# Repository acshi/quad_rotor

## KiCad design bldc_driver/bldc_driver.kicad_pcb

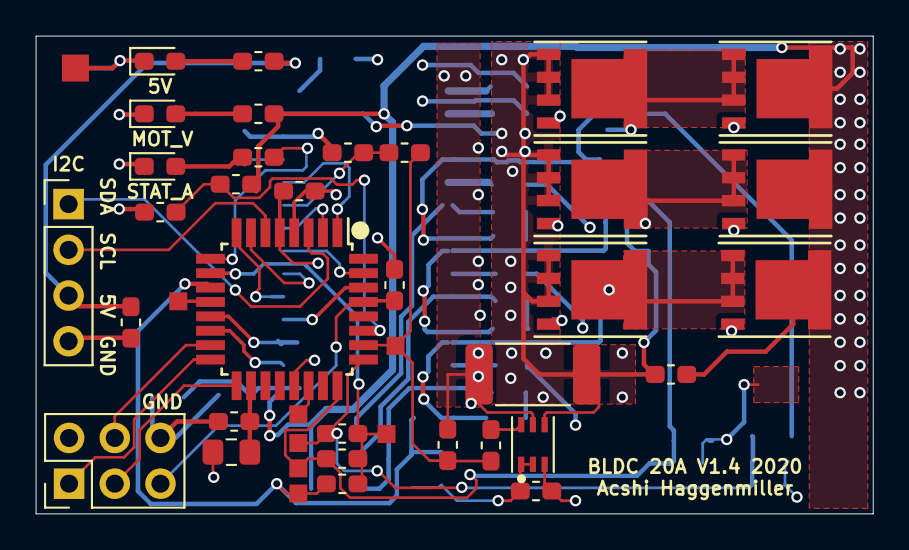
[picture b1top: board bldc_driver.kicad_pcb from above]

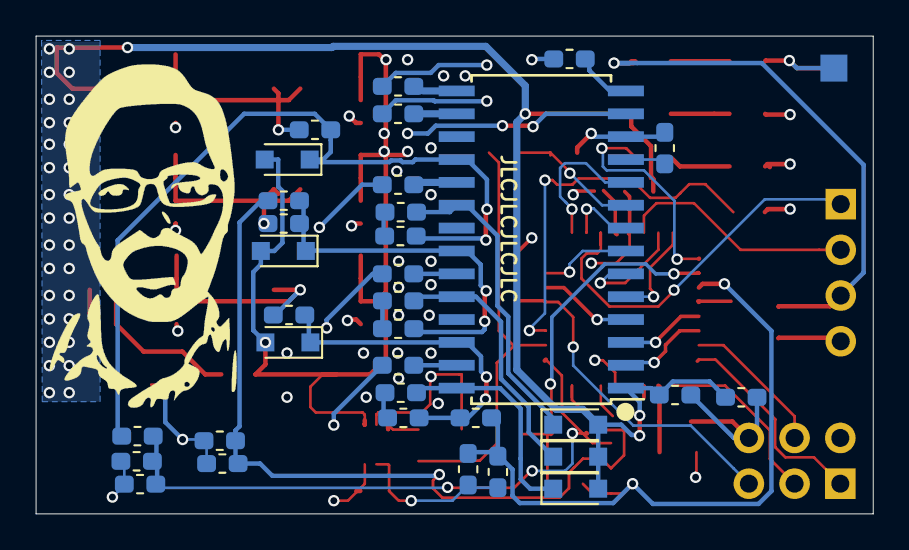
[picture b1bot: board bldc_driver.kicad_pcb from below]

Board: 4 copper layers, 46.5 x 26.5 mm, 67 parts (34 on the bottom side), 56 nets.

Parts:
C2, C5, C6, C16: 100nF; C_0603_1608Metric_Pad1.05x0.95mm_HandSolder
C3, C4, C7, C8: 1uF; C_0603_1608Metric_Pad1.05x0.95mm_HandSolder
C9, C11, C13: 1uF 50V; C_0603_1608Metric_Pad1.05x0.95mm_HandSolder
C10, C12, C14: 22nF; C_0603_1608Metric_Pad1.05x0.95mm_HandSolder
C15: 1nF; C_0603_1608Metric_Pad1.05x0.95mm_HandSolder
D1: Green; LED_0603_1608Metric_Pad1.05x0.95mm_HandSolder
D2: Yellow; LED_0603_1608Metric_Pad1.05x0.95mm_HandSolder
D3: Red; LED_0603_1608Metric_Pad1.05x0.95mm_HandSolder
D4, D5, D6, D7, D8, D9: DSS16UTR‎; D_SOD-323_HandSoldering
J1: I2C 1; PinHeader_1x04_P2.54mm_Vertical
J2: AVR-ISP-6; PinHeader_2x03_P2.54mm_Vertical
L1: 10uH; L_0805_2012Metric_Pad1.15x1.40mm_HandSolder
Q1, Q2, Q3, Q4, Q5, Q6: PSMN0R925YLC; LFPAK_POWER_SO-8
R1, R7: 1k; R_0603_1608Metric_Pad1.05x0.95mm_HandSolder
R2, R6, R11, R18, R22: 4.02k; R_0603_1608Metric_Pad1.05x0.95mm_HandSolder
R3: 3k; R_0603_1608Metric_Pad1.05x0.95mm_HandSolder
R4: 10k; R_0603_1608Metric_Pad1.05x0.95mm_HandSolder
R5, R10, R17, R21: 20k; R_0603_1608Metric_Pad1.05x0.95mm_HandSolder
R8, R12, R19, R23, R24, R25: 1R; R_0603_1608Metric_Pad1.05x0.95mm_HandSolder
R9, R16, R20: 10R; R_0603_1608Metric_Pad1.05x0.95mm_HandSolder
R13, R14, R15: 100k; R_0603_1608Metric_Pad1.05x0.95mm_HandSolder
R26: 20K; R_0603_1608Metric_Pad1.05x0.95mm_HandSolder
R27: 3K; R_0603_1608Metric_Pad1.05x0.95mm_HandSolder
R28, R29, R30: 10; R_0603_1608Metric_Pad1.05x0.95mm_HandSolder
R31: 4mR; R_2512_6332Metric_Pad1.52x3.35mm_HandSolder
U1: ATmega328PB-AU; TQFP-32_7x7mm_P0.8mm
U2: INA199B1; INA199A2
U3: MIC4609; SOIC-28W_7.5x17.9mm_P1.27mm

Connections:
/+5V: C3.1, C4.1, C5.2, J1.3, J2.2, L1.1, R1.2, R4.2, U1.4, U2.3
/+V_MOTOR: C7.2, C8.2, C16.1, D4.2, D5.2, D6.2, Q1.1, Q2.1, Q3.1, R2.2, R5.1, U3.1
/CURRENT: C6.2, R7.1, R26.2, U1.26
/ENABLE: U1.1, U3.10
/HA: U1.14, U3.2
/HB: U1.13, U3.3
/HC: U1.30, U3.4
/LA: U1.8, U3.5
/LB: U1.7, U3.6
/LC: U1.31, U3.7
/MISO: J2.1, U1.16
/MOSI: J2.4, U1.15
/MOTOR_A: C10.1, R10.1, R11.2, R13.2, U1.11
/MOTOR_B: C12.1, R14.2, R17.1, R18.2, U1.24
/MOTOR_C: C14.1, R15.2, R21.1, R22.2, U1.25
/SCK: J2.3, U1.17
/SCL: J1.2, U1.6
/SDA: J1.1, U1.3
/STATUS: R3.2, U1.9
/V_MOT: R5.2, R6.1, U1.27
/bldc_unit1/GHA: Q2.2, R9.1
/bldc_unit1/GHB: Q3.2, R16.1
/bldc_unit1/GHC: Q1.2, R20.1
/bldc_unit1/GLA: Q5.2, R23.1
/bldc_unit1/GLB: Q4.2, R24.1
/bldc_unit1/GLC: Q6.2, R25.1
/bldc_unit1/MOTF_A: D7.1, R8.1, R10.2, R28.1, U3.26
/bldc_unit1/MOTF_B: D8.1, R12.1, R17.2, R29.2, U3.22
/bldc_unit1/MOTF_C: D9.1, R19.1, R21.2, R30.2, U3.18
/bldc_unit1/MOTOR_SHUNT: C16.2, D7.2, D8.2, D9.2, Q4.3, Q5.3, Q6.3, R31.2, U2.4, U3.13
/bldc_unit1/MOTOR_ZERO: R13.1, R14.1, R15.1, U1.10
/bldc_unit1/MOT_A: Q2.3, Q5.1, R28.2
/bldc_unit1/MOT_B: Q3.3, Q4.1, R29.1
/bldc_unit1/MOT_C: Q1.3, Q6.1, R30.1
/~FAULT: U1.2, U3.8
/~RESET: J2.5, R4.1, U1.29
GND: C2.2, C3.2, C4.2, C5.1, C6.1, C7.1, C8.1, C10.2, C12.2, C14.2, C15.1, D1.1, D2.1, D3.1, J1.4, J2.6, R6.2, R11.1, R18.1, R22.1, R27.1, R31.1, U1.5, U1.21, U2.1, U2.2, U2.5, U3.12
unnamed: C2.1, L1.2, U1.18
unnamed: C9.1, D6.1, U3.28
unnamed: C9.2, R8.2
unnamed: C11.1, D5.1, U3.24
unnamed: C11.2, R12.2
unnamed: C13.1, D4.1, U3.20
unnamed: C13.2, R19.2
unnamed: C15.2, U3.11
unnamed: D1.2, R1.1
unnamed: D2.2, R2.1
unnamed: D3.2, R3.1
unnamed: R7.2, U2.6
unnamed: R9.2, U3.27
unnamed: R16.2, U3.23
unnamed: R20.2, U3.19
unnamed: R23.2, U3.16
unnamed: R24.2, U3.15
unnamed: R25.2, U3.14
unnamed: R26.1, R27.2, U3.9

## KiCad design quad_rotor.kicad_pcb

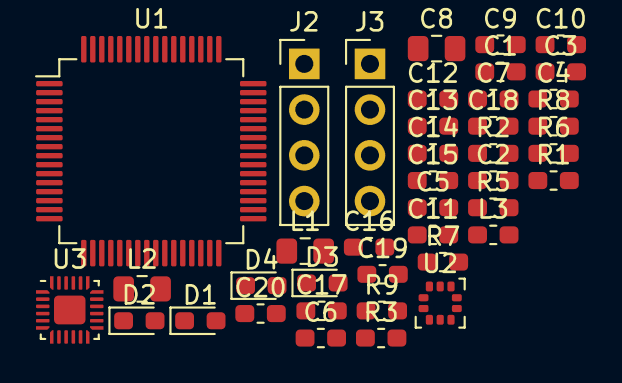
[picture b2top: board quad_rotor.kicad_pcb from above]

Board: 2 copper layers, 40 parts (0 on the bottom side), 17 nets, no tracks yet.

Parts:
C1, C2, C3, C4, C5, C6, C7, C9, C10, C11, C12, C13, C14, C15, C16, C18, C19, C20: 100nF; C_0603_1608Metric_Pad1.05x0.95mm_HandSolder
C8: 4.7uF; C_0805_2012Metric_Pad1.15x1.40mm_HandSolder
C17: 1uF; C_0603_1608Metric_Pad1.05x0.95mm_HandSolder
D1: Green; LED_0603_1608Metric_Pad1.05x0.95mm_HandSolder
D2: Yellow; LED_0603_1608Metric_Pad1.05x0.95mm_HandSolder
D3: Red Forward; LED_0603_1608Metric_Pad1.05x0.95mm_HandSolder
D4: Red Backward; LED_0603_1608Metric_Pad1.05x0.95mm_HandSolder
J2: I2C 1; PinHeader_1x04_P2.54mm_Vertical
J3: I2C 2; PinHeader_1x04_P2.54mm_Vertical
L1, L2: 10uH; L_0805_2012Metric_Pad1.15x1.40mm_HandSolder
L3: 470R@100MHz; L_0603_1608Metric_Pad1.05x0.95mm_HandSolder
R1: 2.2R; R_0603_1608Metric_Pad1.05x0.95mm_HandSolder
R2: 499k; R_0603_1608Metric_Pad1.05x0.95mm_HandSolder
R3: 402k; R_0603_1608Metric_Pad1.05x0.95mm_HandSolder
R5, R6: 100k; R_0603_1608Metric_Pad1.05x0.95mm_HandSolder
R7: 470R; R_0603_1608Metric_Pad1.05x0.95mm_HandSolder
R8: 3.9k; R_0603_1608Metric_Pad1.05x0.95mm_HandSolder
R9: 3k; R_0603_1608Metric_Pad1.05x0.95mm_HandSolder
U1: ATSAMS70J19A; TQFP-64_10x10mm_P0.5mm
U2: LPS25HBTR‎; ST_HLGA-10_2.5x2.5mm_P0.6mm_LayoutBorder3x2y
U3: ICM-20948; QFN-24-1EP_3x3mm_P0.4mm_EP1.75x1.6mm

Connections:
/5V_READ: C1.2, R2.2, R5.1
/+3.3V: C3.1, C4.1, C5.1, C6.1, C7.1, C14.1, C15.1, L2.2, R1.2, U1.4, U1.10, U1.42, U1.58, U1.59, U1.60
/+5V: J2.3, J3.3, R2.1, R7.2
/+V_MOTOR: R3.1, R8.2
/MOT_B: D3.1, D4.2
/SCL: J2.2, J3.2
/SDA: J2.1, J3.1
/VDDCORE: C10.1, C12.1, C13.1, C16.1, C17.1, C19.1, C20.1, L3.2, U1.3, U1.13, U1.24, U1.61
/V_MOTOR_READ: C2.2, R3.2, R6.1
GND: C1.1, C2.1, C3.2, C4.2, C5.2, C6.2, C7.2, C8.1, C9.1, C10.2, C11.1, C12.2, C13.2, C14.2, C15.2, C16.2, C17.2, C18.1, C19.2, C20.2, D1.1, D2.1, J2.4, J3.4, R5.2, R6.2, U1.6, U1.14, U1.31
unnamed: D1.2, R7.1
unnamed: D2.2, R8.1
unnamed: D3.2, D4.1, R9.1
unnamed: L1.1, U1.64
unnamed: L1.2, R1.1
unnamed: L2.1, U1.5
unnamed: L3.1, U1.52

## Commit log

2018-07-03 initial commit of quad rotor project files. mostly working on motor controller so far
2018-08-10 well, missed commit when I fabricated the board, but I have extra parts here to try to fix it... honestly, I should just redesign with mosfet drivers intended for motor use that tolerate negative vol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
2018-08-10 misc changes
2018-09-22 finished v1.1 bldc, sent to make pcb; added components to quad rotor main board
2018-09-25 starting to shave down code for new version of hardware; updated kicad version and files accordingly
2018-09-27 rewrote most code to work with new v1.1 hardware
2018-10-03 debugged and made work the ADC readings and reported values for motor battery voltage and internal temperature
2019-01-02 thinking about adding extra clamping protection to sense pins
2019-01-03 fixed mic4609 footprint, fixed isns bug by giving it divided voltage for current measurement, did not update all pcb footprints to match new ones in schematic from the new kicad library
2019-01-06 added logic level converter for 9 dof imu sensor. some setup for both sensors to use spi
2019-01-09 various testing changes
2019-01-09 new simpler rotor arm should print better
2019-01-29 various intermediate improvements... not stable state
2019-02-12 motors running pretty well in asynchronous mode. only issues now seem to be because of current limits on the power supply. reached about 150hz on motors
2019-03-17 increased speed of AC's fixing the commutation problems. now can go up to 83 percent without trouble
2019-03-28 tried inductive sensing of position... didn't work. starting on subtick timing for better commutation
2019-03-28 moving average filter size based on speed. very fast startup time now
2019-03-28 control of the amount of phase angle preemption to increase speed up and slowdown. tuned for without prop. needs prop tuning
2019-10-02 bldc pdb
2019-10-02 quad rotor pcb
2019-10-02 update to 13 bit adc readings
2019-10-02 scripts
2019-10-02 updates to driver code, 13 bit adc takes longer and doesn't slow down code as much
2019-10-02 scad
2019-10-02 rust driver version. probably obsolete as I'm switching back to AVR
2019-10-03 basic rerouting of new atmega chip on pcb; needs better grounding, more coupling across the two sides, since the ground is a bit tenuous
2019-10-08 added vias and things for grounding
2019-10-18 redo of pcb for atmel micro at 5V to avoid emi problems resetting the old arm. initial conversion of code
2019-10-18 fixed several vias that were still at the wrong size
2020-07-30 driver code working pretty well; some schematic changes started because we need more capacitance on the 5V rail.
2020-10-17 bldc version 1.4 pcb
